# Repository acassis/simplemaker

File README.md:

simplemaker
===========

This is my FirstCNC design!

It is based on http://www.thingiverse.com/thing:41594

This project started as an evolution from TheMarker2 CNC replacing the PIC microcontroller by an Atmega, but eventually I decided to move to this thingiverse design because it is more robust.

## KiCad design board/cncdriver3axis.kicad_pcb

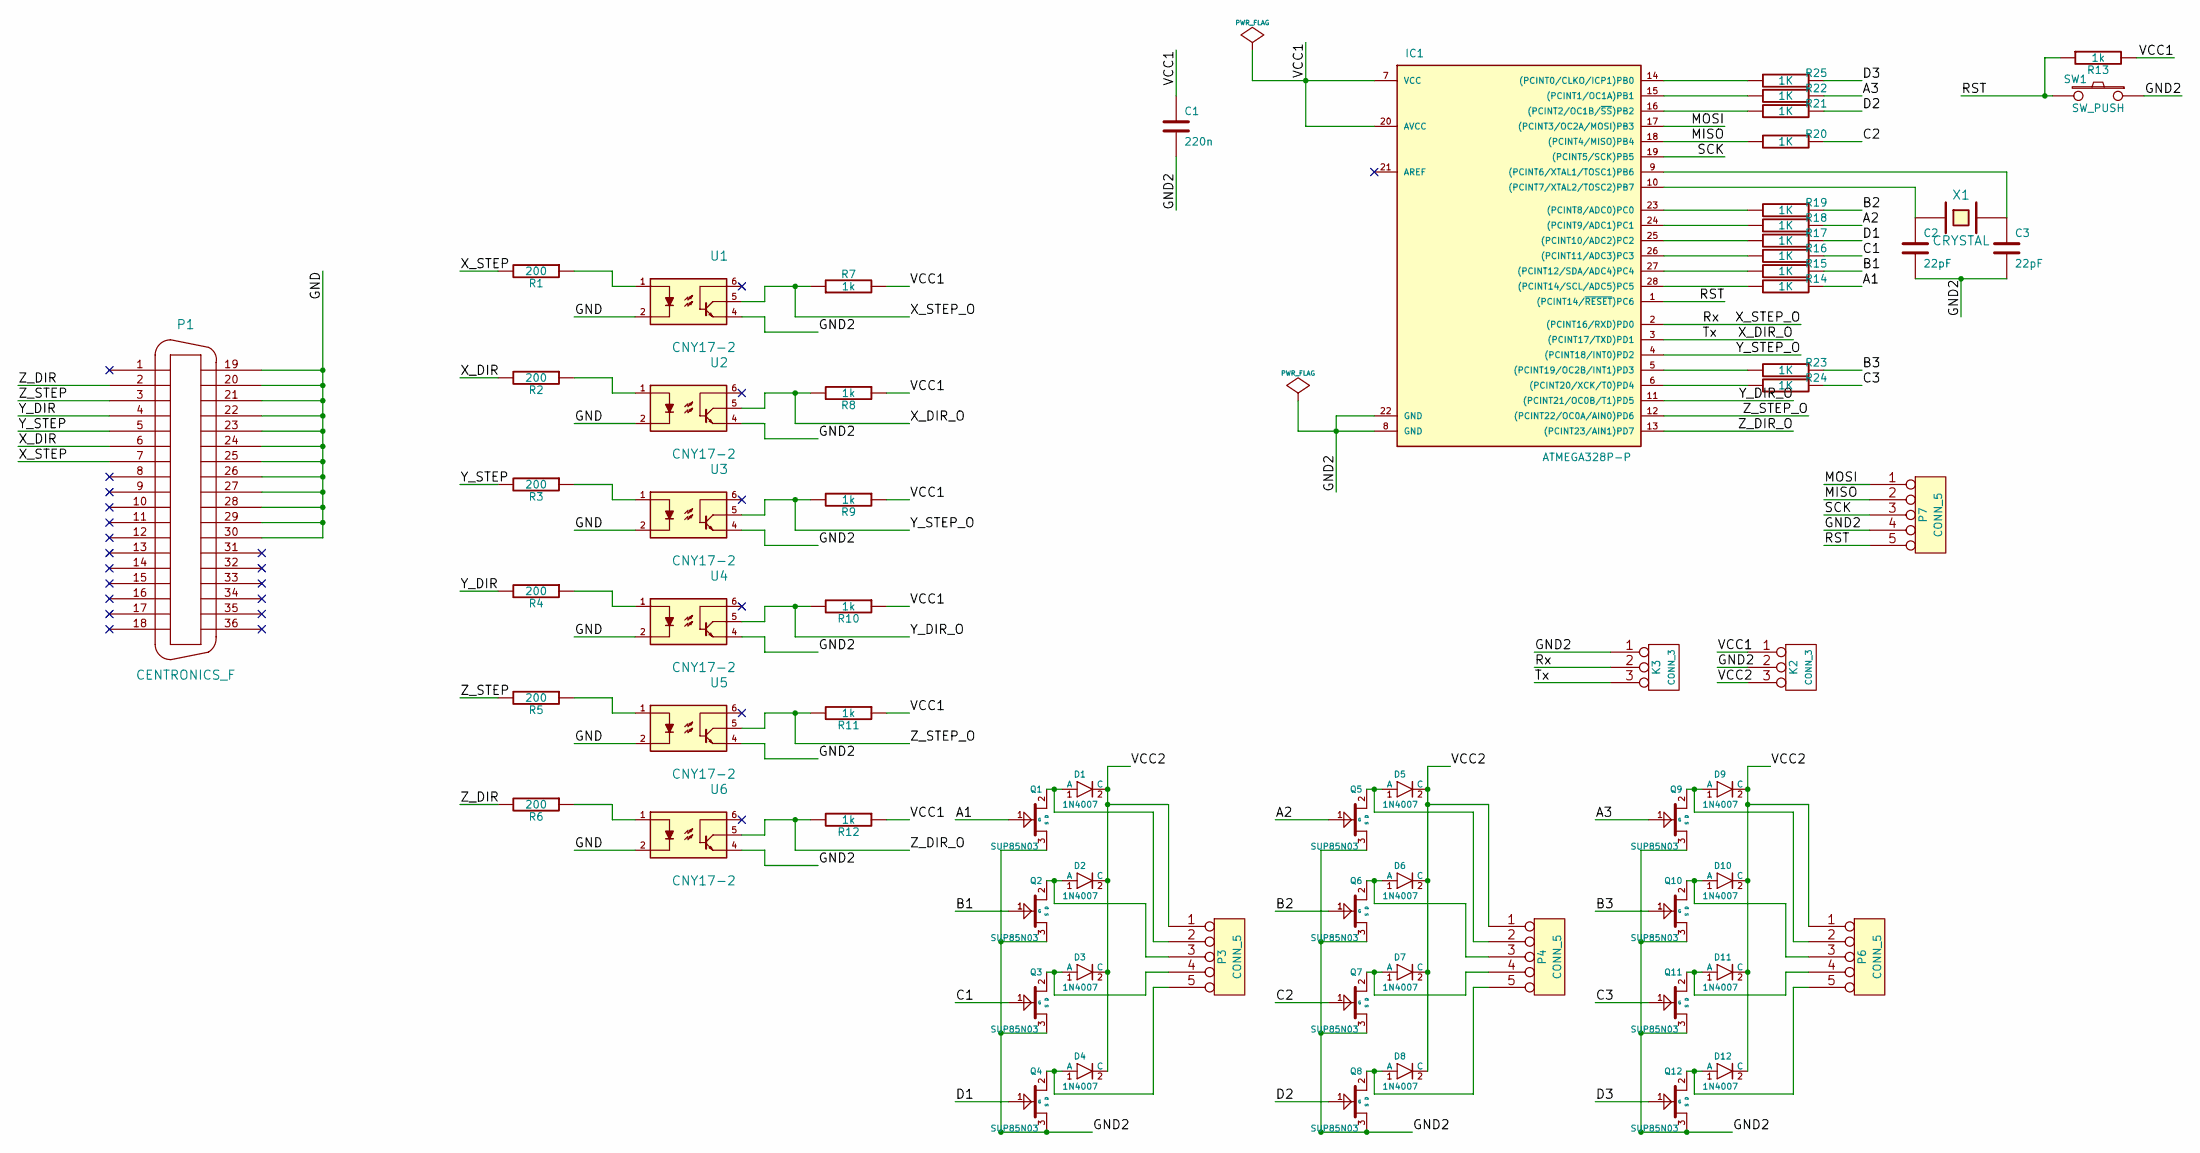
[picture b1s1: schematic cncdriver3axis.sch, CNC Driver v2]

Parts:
C1: 220n
C2, C3: 22pF
D1, D2, D3, D4, D5, D6, D7, D8, D9, D10, D11, D12: 1N4007; DO7
IC1: ATMEGA328P-P; DIL28
K2, K3: CONN_3
P1: CENTRONICS_F
P3, P4, P6, P7: CONN_5
Q1, Q2, Q3, Q4, Q5, Q6, Q7, Q8, Q9, Q10, Q11, Q12: SUP85N03
R1, R2, R3, R4, R5, R6: 200
R7, R8, R9, R10, R11, R12, R13: 1k
R14, R15, R16, R17, R18, R19, R20, R21, R22, R23, R24, R25: 1K
SW1: SW_PUSH
U1, U2, U3, U4, U5, U6: CNY17-2
X1: CRYSTAL

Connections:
/A1: Q1.1 (G), R14.1
/A2: Q5.1 (G), R18.1
/A3: Q9.1 (G), R22.1
/B1: Q2.1 (G), R15.1
/B2: Q6.1 (G), R19.1
/B3: Q10.1 (G), R23.1
/C1: Q3.1 (G), R16.1
/C2: Q7.1 (G), R20.1
/C3: Q11.1 (G), R24.1
/D1: Q4.1 (G), R17.1
/D2: Q8.1 (G), R21.1
/D3: Q12.1 (G), R25.1
/GND: P1.19, P1.20, P1.21, P1.22, P1.23, P1.24, P1.25, P1.26, P1.27, P1.28, P1.29, P1.30, U1.2, U2.2, U3.2, U4.2, U5.2, U6.2
/GND2: C1.2, C2.2, C3.2, IC1.8 (GND), IC1.22 (GND), K2.2 (PM), K3.1, P7.4, Q1.3 (S), Q2.3 (S), Q3.3 (S), Q4.3 (S), Q5.3 (S), Q6.3 (S), Q7.3 (S), Q8.3 (S), Q9.3 (S), Q10.3 (S), Q11.3 (S), Q12.3 (S), SW1.1, U1.4, U2.4, U3.4, U4.4, U5.4, U6.4
/MISO: IC1.18 ((PCINT4/MISO)PB4), P7.2, R20.2
/MOSI: IC1.17 ((PCINT3/OC2A/MOSI)PB3), P7.1
/RST: IC1.1 ((PCINT14/~RESET~)PC6), P7.5, R13.1, SW1.2
/Rx: IC1.2 ((PCINT16/RXD)PD0), K3.2 (PM), R7.1, U1.5
/SCK: IC1.19 ((PCINT5/SCK)PB5), P7.3
/Tx: IC1.3 ((PCINT17/TXD)PD1), K3.3, R8.2, U2.5
/VCC1: C1.1, IC1.7 (VCC), IC1.20 (AVCC), K2.1, R7.2, R8.1, R9.1, R10.1, R11.1, R12.1, R13.2
/VCC2: D1.2 (C), D2.2 (C), D3.2 (C), D4.2 (C), D5.2 (C), D6.2 (C), D7.2 (C), D8.2 (C), D9.2 (C), D10.2 (C), D11.2 (C), D12.2 (C), K2.3, P3.1, P4.1, P6.1
/X_DIR: P1.6, R2.2
/X_STEP: P1.7, R1.2
/Y_DIR: P1.4, R4.2
/Y_DIR_O: IC1.11 ((PCINT21/OC0B/T1)PD5), R10.2, U4.5
/Y_STEP: P1.5, R3.2
/Y_STEP_O: IC1.4 ((PCINT18/INT0)PD2), R9.2, U3.5
/Z_DIR: P1.2, R6.2
/Z_DIR_O: IC1.13 ((PCINT23/AIN1)PD7), R12.2, U6.5
/Z_STEP: P1.3, R5.2
/Z_STEP_O: IC1.12 ((PCINT22/OC0A/AIN0)PD6), R11.2, U5.5
unnamed: R2.1, U2.1
unnamed: R4.1, U4.1
unnamed: R6.1, U6.1
unnamed: D4.1 (A), P3.5, Q4.2 (D)
unnamed: R1.1, U1.1
unnamed: R5.1, U5.1
unnamed: D10.1 (A), P6.3, Q10.2 (D)
unnamed: D5.1 (A), P4.2, Q5.2 (D)
unnamed: IC1.5 ((PCINT19/OC2B/INT1)PD3), R23.2
unnamed: IC1.6 ((PCINT20/XCK/T0)PD4), R24.2
unnamed: R3.1, U3.1
unnamed: D6.1 (A), P4.3, Q6.2 (D)
unnamed: D8.1 (A), P4.5, Q8.2 (D)
unnamed: D7.1 (A), P4.4, Q7.2 (D)
unnamed: D2.1 (A), P3.3, Q2.2 (D)
unnamed: IC1.14 ((PCINT0/CLKO/ICP1)PB0), R25.2
unnamed: IC1.24 ((PCINT9/ADC1)PC1), R18.2
unnamed: IC1.27 ((PCINT12/SDA/ADC4)PC4), R15.2
unnamed: IC1.25 ((PCINT10/ADC2)PC2), R17.2
unnamed: C3.1, IC1.9 ((PCINT6/XTAL1/TOSC1)PB6), X1.2
unnamed: D9.1 (A), P6.2, Q9.2 (D)
unnamed: D11.1 (A), P6.4, Q11.2 (D)
unnamed: D12.1 (A), P6.5, Q12.2 (D)
unnamed: C2.1, IC1.10 ((PCINT7/XTAL2/TOSC2)PB7), X1.1
unnamed: IC1.28 ((PCINT14/SCL/ADC5)PC5), R14.2
unnamed: IC1.16 ((PCINT2/OC1B/~SS~)PB2), R21.2
unnamed: IC1.15 ((PCINT1/OC1A)PB1), R22.2
unnamed: IC1.23 ((PCINT8/ADC0)PC0), R19.2
unnamed: IC1.26 ((PCINT11/ADC3)PC3), R16.2
unnamed: D1.1 (A), P3.2, Q1.2 (D)
unnamed: D3.1 (A), P3.4, Q3.2 (D)

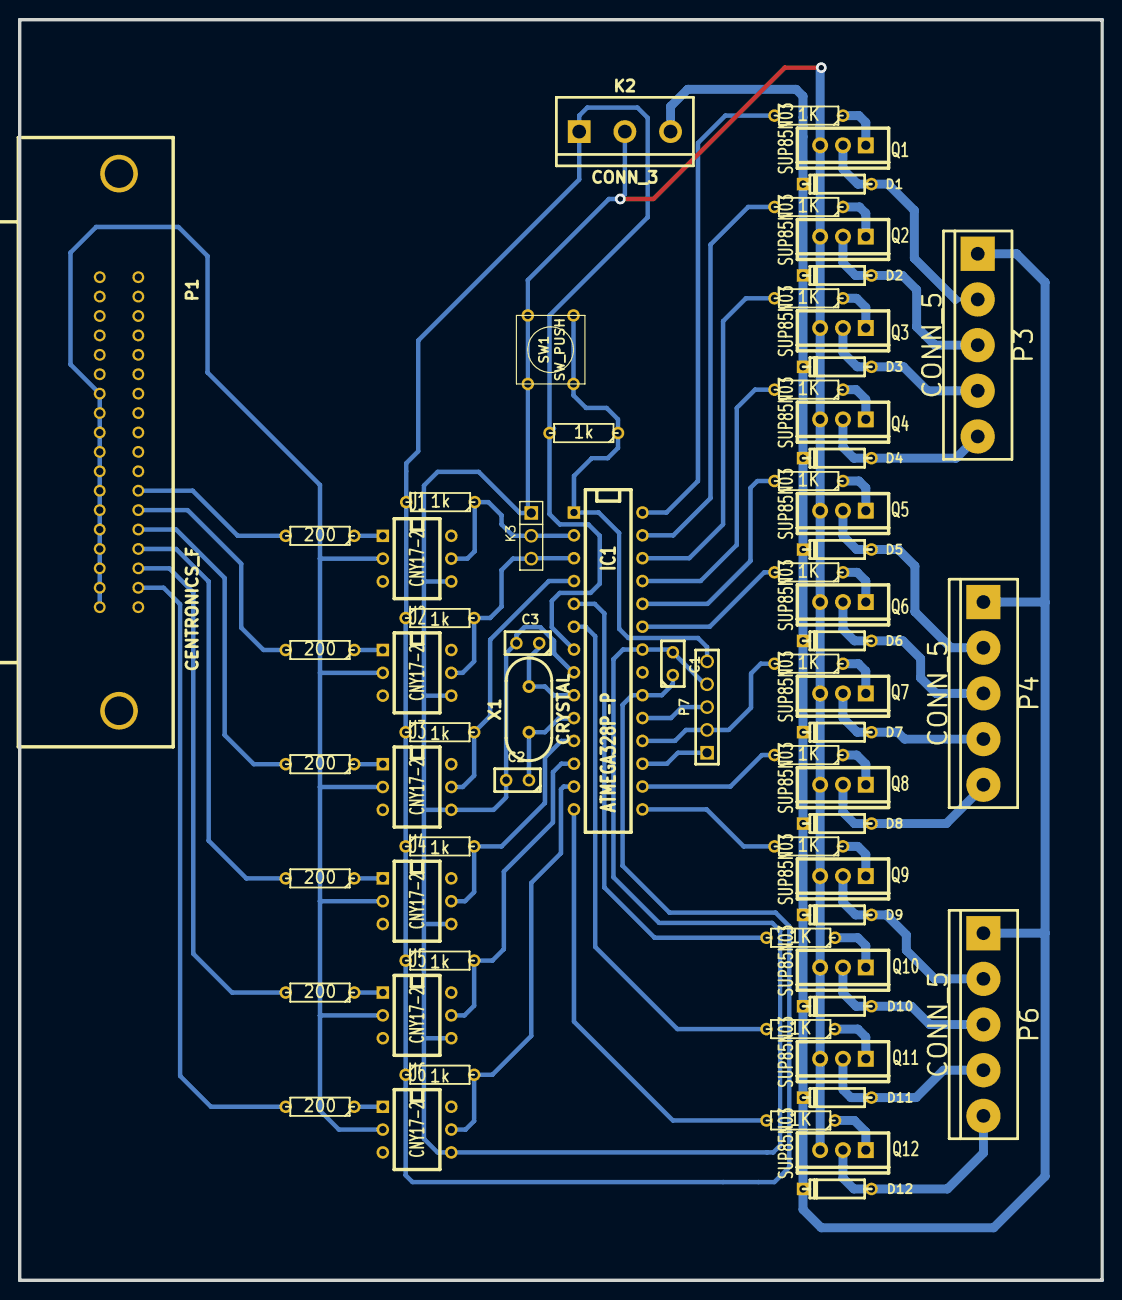
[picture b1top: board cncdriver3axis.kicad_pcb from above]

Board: 2 copper layers, 120.4 x 140.2 mm, 68 parts (0 on the bottom side), 63 nets.

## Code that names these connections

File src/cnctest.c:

#include <avr/io.h>
#include <util/delay.h>

#ifndef F_CPU
#define F_CPU 16000000UL           /* Clock Frequency = 16Mhz */
#endif

#define SPEED 9600

#define X_STEP (1 << 0)
#define X_DIR  (1 << 1)

#define Y_STEP (1 << 2)
#define Y_DIR  (1 << 5)

#define Z_STEP (1 << 6)
#define Z_DIR  (1 << 7)

int modeX = 0;
int stepX = 0;

int modeY = 0;
int stepY = 0;

int modeZ = 0;
int stepZ = 0;

#define A1(N)	do { PORTC &= ~(_BV(PC5)); PORTC |= (N << PC5); } while(0)
#define B1(N)	do { PORTC &= ~(_BV(PC4)); PORTC |= (N << PC4); } while(0)
#define C1(N)	do { PORTC &= ~(_BV(PC3)); PORTC |= (N << PC3); } while(0)
#define D1(N)	do { PORTC &= ~(_BV(PC2)); PORTC |= (N << PC2); } while(0)

#define A2(N)	do { PORTC &= ~(_BV(PC1)); PORTC |= (N << PC1); } while(0)
#define B2(N)	do { PORTC &= ~(_BV(PC0)); PORTC |= (N << PC0); } while(0)
#define C2(N)	do { PORTB &= ~(_BV(PB4)); PORTB |= (N << PB4); } while(0)
#define D2(N)	do { PORTB &= ~(_BV(PB2)); PORTB |= (N << PB2); } while(0)

#define A3(N)	do { PORTB &= ~(_BV(PB1)); PORTB |= (N << PB1); } while(0)
#define B3(N)	do { PORTD &= ~(_BV(PD3)); PORTD |= (N << PD3); } while(0)
#define C3(N)	do { PORTD &= ~(_BV(PD4)); PORTD |= (N << PD4); } while(0)
#define D3(N)	do { PORTB &= ~(_BV(PB0)); PORTB |= (N << PB0); } while(0)


void changeStepX(int dir){
	if(dir)
		stepX = (++stepX) % 4;
	else
		stepX = (--stepX) % 4;
	
	if(stepX==0){
		A1(1);
		B1(1);
		C1(0);
		D1(0);
	}else if(stepX==1){
		A1(0);
		B1(1);
		C1(1);
		D1(0);
	}else if(stepX==2){
		A1(0);
		B1(0);
		C1(1);
		D1(1);
	}else if(stepX==3){
		A1(1);
		B1(0);
		C1(0);
		D1(1);
	}
}

void changeStepY(int dir){
	if(dir)
		stepY = (++stepY) % 4;
	else
		stepY = (--stepY) % 4;
	
	if(stepY==0){
		A2(1);
		B2(1);
		C2(0);
		D2(0);
	}else if(stepY==1){
		A2(0);
		B2(1);
		C2(1);
		D2(0);
	}else if(stepY==2){
		A2(0);
		B2(0);
		C2(1);
		D2(1);
	}else if(stepY==3){
		A2(1);
		B2(0);
		C2(0);
		D2(1);
	}
}

void changeStepZ(int dir){
	if(dir)
		stepZ = (++stepZ) % 4;
	else
		stepZ = (--stepZ) % 4;
	
	if(stepZ==0){
		A3(1);
		B3(1);
		C3(0);
		D3(0);
	}else if(stepZ==1){
		A3(0);
		B3(1);
		C3(1);
		D3(0);
	}else if(stepZ==2){
		A3(0);
		B3(0);
		C3(1);
		D3(1);
	}else if(stepZ==3){
		A3(1);
		B3(0);
		C3(0);
		D3(1);
	}
}

static void serial_init(unsigned int bittimer)
{
	/* Set the baud rate */
	UBRR0H = (unsigned char) (bittimer >> 8);
	UBRR0L = (unsigned char) bittimer;
	/* set the framing to 8N1 */
	UCSR0C = (3 << UCSZ00);
	/* Engage! */
	UCSR0B = (1 << RXEN0) | (1 << TXEN0);
	return;
}

static void serial_write(unsigned char c)
{
	while ( !(UCSR0A & (1 << UDRE0)) )
		;
	UDR0 = c;
}

int main (void)
{

	int i = 0;
	char *str
          = "XS = X XD = X YS = Y YD = Y ZS = Z ZD = Z\r\n";

	/* set PORTB for output*/
	DDRB = 0xFF;

	/* set PORTC for output*/
	DDRC = 0xFF;

	/* set PORTD[0,1,2,5,6,7] for input and PORTD[3,4] output*/
	DDRD = 0x18;

        /* set pull-up for all input pins */
	PORTD = ~(0x18);

	/* let the preprocessor calculate this */
	serial_init( ( F_CPU / SPEED / 16 ) - 1);

	if(PIND & X_STEP){
		modeX = 1;
	}else{
		modeX = 0;
	}
	
	if(PIND & Y_STEP){
		modeY = 1;
	}else{
		modeY = 0;
	}	
	
	if(PIND & Z_STEP){
		modeZ = 1;
	}else{
		modeZ = 0;
	}	

	modeZ = 0;
	
	while(1){
		if(modeX == 0){
			if(PIND & X_STEP){
				modeX = 1;
				if(PIND & X_DIR){
					changeStepX(1);
				}else{
					changeStepX(0);
				}
			}
					
		}else{
			if(!(PIND & X_STEP)){
				modeX = 0;
			}
		}
	
		if(modeY == 0){
			if(PIND & Y_STEP){
				modeY = 1;
				if(PIND & Y_DIR){
					changeStepY(1);
				}else{
					changeStepY(0);
				}
			}
					
		}else{
			if(!(PIND & Y_STEP)){
				modeY = 0;
			}
		}		
		
		if(modeZ == 0){
			if(PIND & Z_STEP){
				modeZ = 1;
				if(PIND & Z_DIR){
					changeStepZ(1);
				}else{
					changeStepZ(0);
				}
			}
					
		}else{
			if(!(PIND & Z_STEP)){
				modeZ = 0;
			}
		}		
		
	}

	/* while (1) {

		if (PIND & X_STEP)
			str[5]='1';
		else
			str[5]='0';

		if (PIND & X_DIR)
			str[12]='1';
		else
			str[12]='0';


		if (PIND & Y_STEP)
			str[19]='1';
		else
			str[19]='0';

		if (PIND & Y_DIR)
			str[26]='1';
		else
			str[26]='0';


		if (PIND & Z_STEP)
			str[33]='1';
		else
			str[33]='0';

		if (PIND & Z_DIR)
			str[40]='1';
		else
			str[40]='0';


		//USART_putstring(str);
		serial_write(str[i++]);
		if (str[i] == '\0') {
			i = 0;
			_delay_ms(500);
		}

	}*/
	return 0;
}

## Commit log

2013-12-01 Initial commit to add schematic and source code of SimpleMaker
2014-02-14 Add FreeCAD design
2014-02-14 Update the readme file
2014-02-14 Update README file
